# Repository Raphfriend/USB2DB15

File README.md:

# USB2DB15 - Supergun Adapter  

A simple ATmega328P-based USB-to-DB15 adapter designed for use with a Supergun or Neo Geo system.

<p align="center">
  
 <br>
  <b>USB2DB15 with a Sega Astro City Mini Arcade Stick</b><br>
<br>
	</p>  	

### 1. Features:

- USB input to support most modern HID compatible controllers
- 1ms polling, meaning a low latency and fast response from the USB2DB15
- Open-source firmware, so everyone in the community can collaborate
- DB15 pinout standard, ready for Neo Geo, Minigun, and HAS Superguns
- 4 customizable and storable mapping configurations
- 10 customizable and storable controller profiles
- Status LED
- Protection circuit for your beloved controllers

### 2. Technical information:

The USB2DB15 adapter is an open-source device based on an AVR microcontroller. It adapts a USB controller for use with a JAMMA PCB through a Supergun or with Neo Geo hardware that has controller ports. A variety of common controllers are supported, including controllers that follow the PS3/PS4 DualShock, PS5 DualSense, and Xbox 360/One protocols. Due to the diversity of controllers and differing standards, some controllers may not work with USB2DB15 or may not work as intended. Please be patient during these early stages. Feel free to contact the developers with additional information or requests for help with your USB2DB15 adapter through our communication channels (GitHub, Discord, and the Arcade-Projects forum).

We are using a modified USB Host Shield 2.0 library for controller IDs that aren't natively supported.

The 8BitDo M30 Mega Drive and NEOGEO controllers are supported through their original 2.4 GHz USB receivers and through a wired USB connection. The receiver versions use XInput mode; the wired versions use their USB controller mode.

With regard to hardware, there are currently three options:

- A Custom PCB that accommodates and integrates an Arduino Pro Mini, USB Shield Mini and other relevant hardware.
- USB2DB15 2.0 Ver, a pre-built single PCB that incorporates all required hardware in a standalone form.
- USB2DB15 CS Ver, similar to 2.0 Ver but focused on PCB consolization. In place of the DB15 controller connector, this board has screw terminals and a 20-pin header compatible with a 20-pin Brook Fighting Board Cable.

Alternatively, you can simply use a breadboard to connect it all together.

If you are building the open source version for yourself, a basic understanding of Arduino and its programming environment is required. Visit [arduino.cc](https://arduino.cc) to help you get started.

<p align="center">
  
 <br>
  <b>USB2DB15 pinout standard</b><br>
<br>

### 3. Open Source Required Hardware:

* The USB2DB15 uses an ATmega328P AVR. Any Arduino that uses this microcontroller, such as the Pro Mini, Nano, or Uno, is suitable. The custom PCB accommodates an Arduino Pro Mini and USB Host Shield Mini.
* USB Host Shield Mini if using an Arduino Pro Mini / Nano. Full sized USB Host Shield for Uno.
* An FTDI programmer is required for the Arduino Pro Mini. This is not required if using an Arduino Nano or Uno.
* A USB2DB15 custom PCB or a breadboard to complete all connections between the AVR and USB Host Shield.
* DB15 female connector.

<p align="center">
  
 <br>
  <b>Arduino Pro Mini and Usb Host Shield Mini</b><br>
<br>
	</p>  	

If using the custom PCB with an Arduino Pro Mini and USB Host Shield Mini, a BOM is available in the repository's `BOM` folder.

##### Jumper settings:

- SJ1: Bridge this jumper ONLY to disable 5V protection.
- SJ2: Bridge this jumper ONLY to enable 5V protection.
- JP2: 5V solder point (see information below regarding USB VBUS).

Due to variations among Pro Mini PCBs, A4 and A5 may be in different locations. Please pay attention to this.

<p align="center">

 <br>
  <b>Custom PCB 1.2 for Arduino Pro Mini</b><br>
</p>

### 4. Installation:

Download the <a href="https://github.com/Raphfriend/USB_Host_Shield_2.0">USB Host Shield 2.0 library</a> and install it in the Arduino IDE. Open the INO file (`RFUSB_to_DB15.ino`) and upload it to your AVR.

If you have a USB Host Shield Mini, you will need to cut the trace after the 2.2 kΩ resistor near the USB VBUS pin. Solder a wire from JP2 on the custom PCB to the through-hole via labeled `5V`, as shown in the picture below.

This enables devices that require +5 V power to function correctly, because the USB Host Shield Mini supplies only 3.3 V to the VBUS pin of the USB connector by default.

The remainder is plug and play.

If you are not using a prefabricated PCB, see the schematic for wiring information.

#### 4.1. Arduino Pro Mini + USB Shield Mini:
[See FLASHING.md for instructions.](FLASHING.md)

#### 4.2. Arduino Uno + USB Host Shield:

1. Install Arduino IDE.
2. Mount the USB Host Shield to the Arduino Uno correctly.
3. Connect the Arduino Uno to your PC via its USB Type-B cable.
4. In the Arduino IDE, navigate to "Tools" -> "Board" -> "Arduino AVR Boards" and select "Arduino Uno".
5. In the Arduino IDE, navigate to "Tools" -> "Port" and choose the Arduino device.
6. In the Arduino IDE, navigate to "Tools" -> "Programmer" and select "AVRISP MKII".
7. Find the library path in Arduino IDE: "File" -> "Preferences" -> "Sketchbook location", then copy the required `USB_Host_Shield_20` library into the `libraries` directory.
8. Open the firmware INO file (`RFUSB_to_DB15.ino`).
9. With the Arduino Uno connected to your PC, select "Sketch" -> "Upload".
10. Wait for the sketch to upload, as indicated in the console window at the bottom of the Arduino IDE.

### 5. Supported Controllers:

[See Compatibility.md for a detailed list of supported controllers.](COMPATIBILITY.md)

#### 5.1. DualShock 4 and DualSense left analog stick

USB DualShock 4 and DualSense controllers can use the left analog stick as an additional digital directional input. The analog stick and physical D-pad are combined, so either input can control the DB15 directions.

For these controllers, the firmware applies Hit Box-style SOCD cleaning after combining both directional sources:

| Simultaneous directions | DB15 output |
| --- | --- |
| Left + Right | Neutral |
| Up + Down | Up |

This prevents opposite horizontal directions from reaching the game and makes vertical conflicts deterministic. The feature is enabled automatically for supported DualShock 4 and DualSense USB reports; no separate profile or user configuration is required.

#### 5.2. Release mode and Serial diagnostics

`RFUSB_to_DB15/BuildConfig.h` contains the following build-time setting:

```cpp
#define USB2DB15_RELEASE_MODE 1
```

Use release mode (`1`) for competitive play. It disables all firmware Serial output, preventing diagnostic messages from occupying the serial transmit buffer and delaying controller polling or DB15 updates.

Use diagnostic mode (`0`) when troubleshooting a controller:

```cpp
#define USB2DB15_RELEASE_MODE 0
```

Upload the firmware again after changing the setting, then open the Arduino Serial Monitor at 115200 baud. Set the value back to `1` and upload again before competitive play.

### 6. Software Usage
#### 6.1 Controller Profiles
The adapter can store profiles for up to 10 unique controller models*. Controllers of the same make and model share profiles.
Each controller has 4 associated profiles. If you plug in an 11th controller, the system replaces the oldest controller you have set up, then the next oldest for the 12th, and so on. This may require you to set up older controllers again when you resume using them.

These can be accessed by pressing SELECT (COIN) plus one of the four directions.
For example, press SELECT + UP for the first profile, SELECT + RIGHT for the second, and so on.
The adapter will remember what profile you were using and automatically switch to it when you use the controller again.

To change a profile's key bindings, first switch to the profile you want to set up.
While holding SELECT for at least 3 seconds, press buttons 1–6 in order. Then release SELECT to lock in the binding.

*XBox One controllers appear to the system as the same make and model and thus use the same profiles even if they are different controllers.

### Shell

[AvramCE](https://twitter.com/avramce) has created a [3D printed case](https://www.thingiverse.com/thing:5170415) that you can print for your USB2DB15.

### How does it look in real life?

When you put all the parts together, USB2DB15 should look like this.
<p align="center">
  
	 <br>
  <b>Setup and photo by <a href="https://twitter.com/Focux11">@Focux</a> </b>
	</p>  	
<p align="center">
  
	 <br>
    <b>Setup and photo by <a href="https://twitter.com/_atrac17">@_atrac17</a> </b>
	</p>  	

### Support this project

If you have found USB2DB15 useful, please consider funding it and making a donation so that we may continue our work by obtaining additional controllers, equipment, and everything else required to keep this project alive and growing.

### Is this product available to buy? Yes!

We sell USB2DB15 directly. You will receive a premium edition that is slightly different from the open-source version but has the same features.
You can choose from a variety of shell color options, and you will get detailed instructions following your purchase.
There are two versions: the standard DB15 and the CS Ver., which is targeted toward JAMMA PCB consolization.

<a href="https://ko-fi.com/s/b6c3d01043">Access our shop by clicking here or on the images below. </a>

<p align="center">
<a href="https://ko-fi.com/s/b6c3d01043">
  
</p>

<p align="center">
<a href="https://ko-fi.com/s/b6c3d01043">
  
</p>

<p align="center">
<a href="https://ko-fi.com/s/b6c3d01043">
  
</p>

<p align="center">
<a href="https://ko-fi.com/s/b6c3d01043">
  
</p>

### Where can I get more help if I need it?

Via Arcade-Projects forum or RF Projects Discord server.

<p align="center">
<a href="https://www.arcade-projects.com/forums/index.php?thread/14205-open-source-usb-to-db15-for-supergun-adapter/">
  
</p>

<p align="center">
<a href="https://discord.gg/XKCjtpH">
  
</p>

### LEGAL

Neither USB2DB15 nor any of its maintainers is associated with or endorsed by Nintendo, Sony, SNK, Microsoft, 8BitDo, Sega, Brook, Mad Catz, Nacon, Honcam, DaemonBite, Buffalo, Qanba, Razer, Retro-Bit, Toodles, Hori, or any other company not explicitly indicated. All other brands and product names are the property of their respective holders.

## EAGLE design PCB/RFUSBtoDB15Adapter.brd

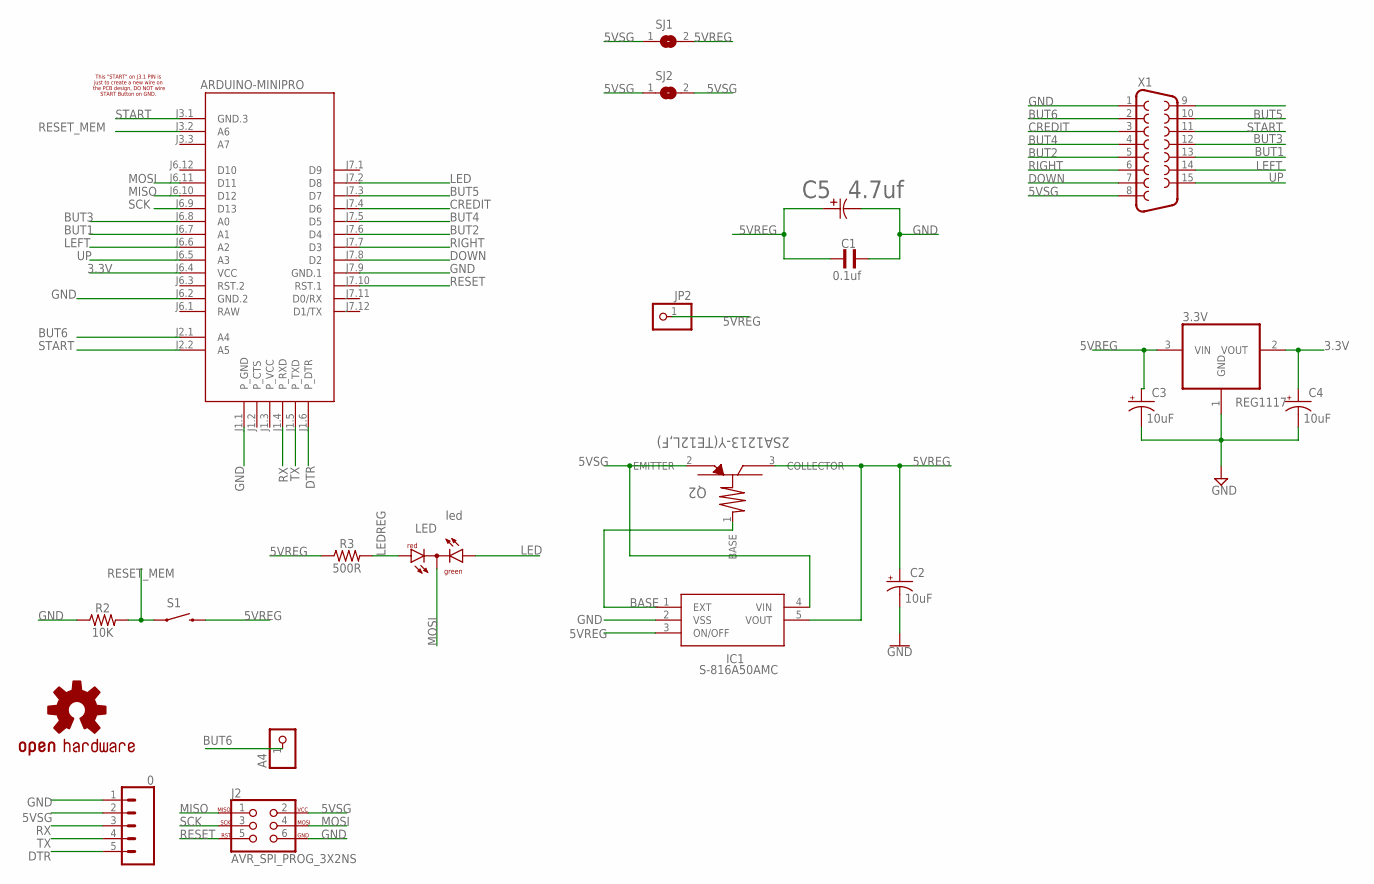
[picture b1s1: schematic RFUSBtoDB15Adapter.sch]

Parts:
3.3V: REG1117; SOT223
A4: 0; 1X01
ARDUINO-MINIPRO: ARDUINO-PRO-MINI-5.0V; ARDUINO-PRO-MINI
C1: 0.1uf; WCAP-CSGP_0805_REFLOW
C2, C3, C4: 10uF; EIA3216
C5: 4.7uf; CAPMP3.4X1.6_1.8N_KEM
IC1: S-816A40AMC-BAPT2U; SOT95P275X130-5N; MANUFACTURER_PART_NUMBER S-816A50AMC
J1: 0; 1X05
J2: AVR_SPI_PROG_3X2NS; 2X3-NS
JP2: JP2; 1X01
LED: led; DUOLED-C-5MM
LOGO1: OSHW-LOGOS; OSHW-LOGO-S
Q2: 2SA1213-Y(TE12L,F); PW-MINI_TOS
R2: 10K; 0805
R3: 500R; 0805
S1: RS032G05A3SM-SPST-MOMENTARY-SWSMD-1101NE; TACTILE-SWITCH-1101NE
SJ1, SJ2: SJ
X1: F15HP

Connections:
3.3V: 3.3V.2 (VOUT), ARDUINO-MINIPRO.J6.4 (VCC), C4.+
5VREG: 3.3V.3 (VIN), C1.2, C2.+, C3.+, C5.1, IC1.3 (ON/OFF), IC1.5 (VOUT), JP2.1, Q2.3 (COLLECTOR), R3.1, S1.2, SJ1.2
5VSG: IC1.4 (VIN), J1.2, J2.2, Q2.2 (EMITTER), SJ1.1, SJ2.1, SJ2.2, X1.8
BASE: IC1.1 (EXT), Q2.1 (BASE)
BUT1: ARDUINO-MINIPRO.J6.7 (A1), X1.13
BUT2: ARDUINO-MINIPRO.J7.6 (D4), X1.5
BUT3: ARDUINO-MINIPRO.J6.8 (A0), X1.12
BUT4: ARDUINO-MINIPRO.J7.5 (D5), X1.4
BUT5: ARDUINO-MINIPRO.J7.3 (D7), X1.10
BUT6: A4.1, ARDUINO-MINIPRO.J2.1 (A4), X1.2
CREDIT: ARDUINO-MINIPRO.J7.4 (D6), X1.3
DOWN: ARDUINO-MINIPRO.J7.8 (D2), X1.7
DTR: ARDUINO-MINIPRO.J1.6 (P_DTR), J1.5
GND: 3.3V.1 (GND), ARDUINO-MINIPRO.J1.1 (P_GND), ARDUINO-MINIPRO.J6.2 (GND.2), ARDUINO-MINIPRO.J7.9 (GND.1), C1.1, C2.-, C3.-, C4.-, C5.2, IC1.2 (VSS), J1.1, J2.6, R2.1, X1.1
LED: ARDUINO-MINIPRO.J7.2 (D8), LED.AX (AG)
LEDREG: LED.AR, R3.2
LEFT: ARDUINO-MINIPRO.J6.6 (A2), X1.14
MISO: ARDUINO-MINIPRO.J6.10 (D12), J2.1
MOSI: ARDUINO-MINIPRO.J6.11 (D11), J2.4, LED.C
RAW: ARDUINO-MINIPRO.J6.1 (RAW)
RESET: ARDUINO-MINIPRO.J7.10 (RST.1), J2.5
RESET_MEM: ARDUINO-MINIPRO.J3.2 (A6), R2.2, S1.1
RIGHT: ARDUINO-MINIPRO.J7.7 (D3), X1.6
RX: ARDUINO-MINIPRO.J1.4 (P_RXD), J1.3
SCK: ARDUINO-MINIPRO.J6.9 (D13), J2.3
START: ARDUINO-MINIPRO.J2.2 (A5), ARDUINO-MINIPRO.J3.1 (GND.3), X1.11
TX: ARDUINO-MINIPRO.J1.5 (P_TXD), J1.4
UP: ARDUINO-MINIPRO.J6.5 (A3), X1.15

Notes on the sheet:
This "START" on J3.1 PIN is just to create a new wire on the PCB design, DO NOT wire START Button on GND.

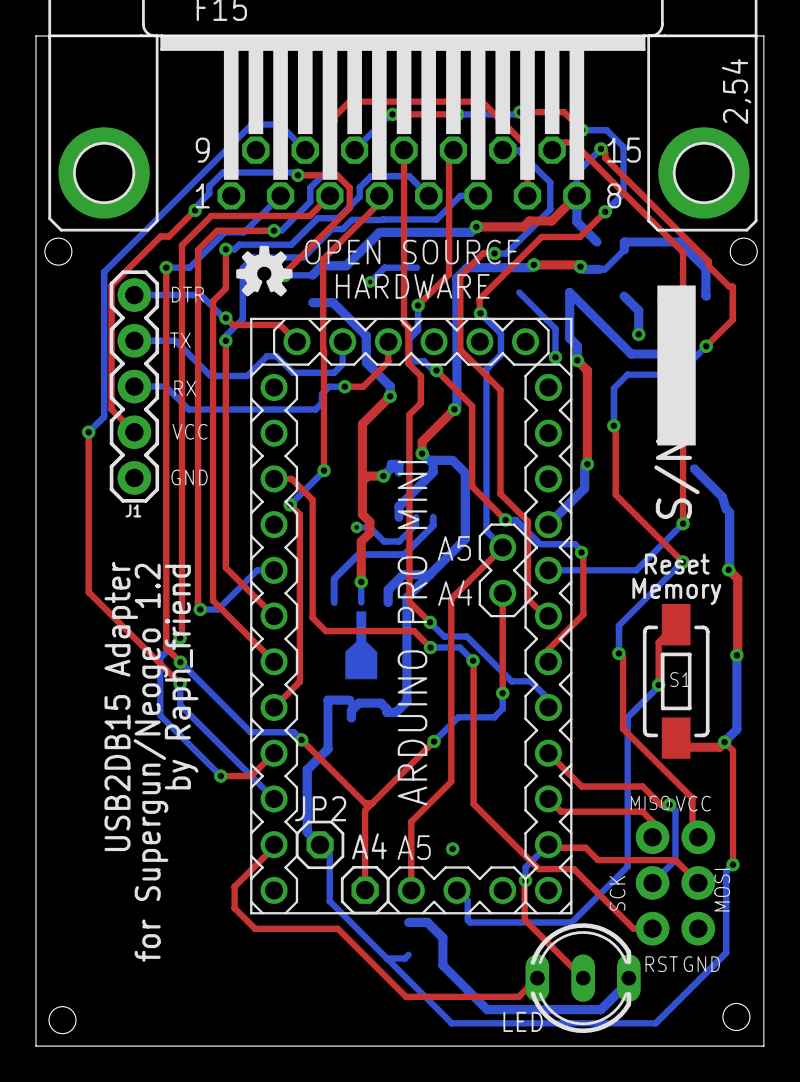
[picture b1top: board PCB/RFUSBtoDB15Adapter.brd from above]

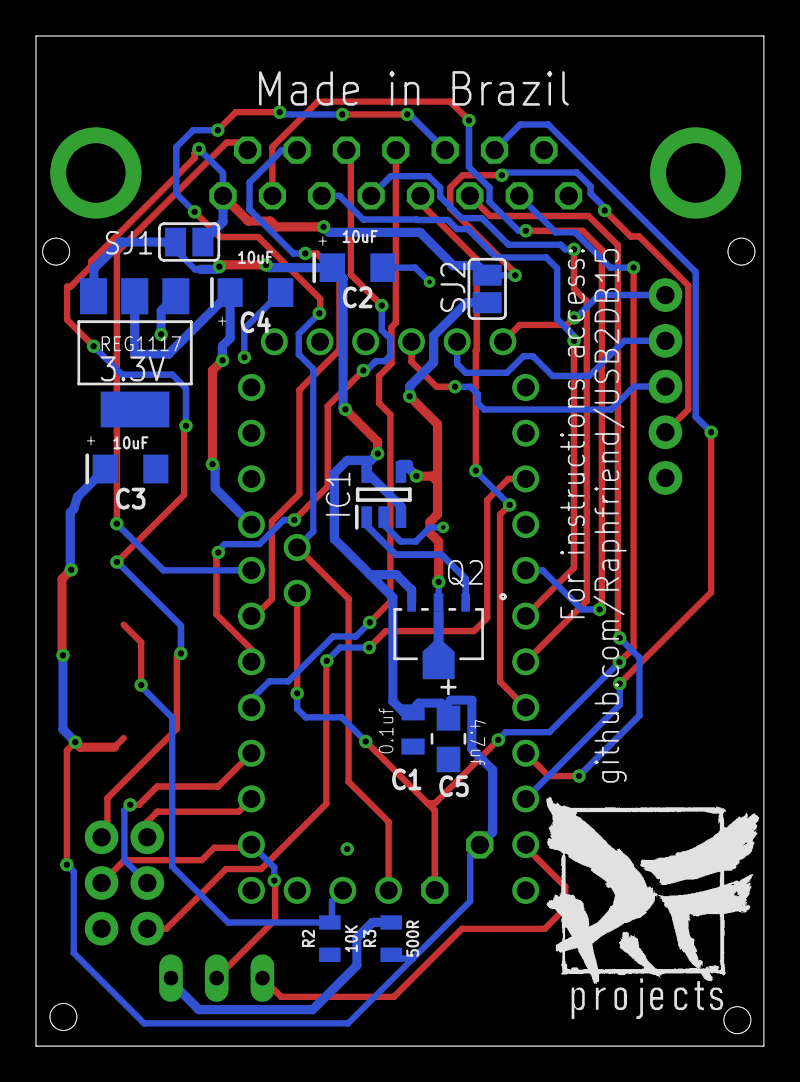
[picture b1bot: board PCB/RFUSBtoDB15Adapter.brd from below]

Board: 2 copper layers, 40.4 x 56.1 mm, 22 parts (13 on the bottom side), 27 nets.

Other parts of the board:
U$2: RF_LOGO

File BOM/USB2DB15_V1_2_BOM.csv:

Designator,Component,Footprint,LCSC Part #
3.3V,REG1117,SOT223,
IC1,S-816A40AMC-BAPT2U,SOT95P275X130-5N,
Q2,2SA1213-Y(TE12L F),PW-MINI_TOS,
C1,0.1uf,0805 SMD Ceramic,
"C2, C3 and C4 are optional",10uF,EIA3216,
C5,4.7uf,CAPMP3.4X1.6_1.8N_KEM,
R2,10K,0805 SMD,
R3,33R-500R,0805 SMD,
S1,TACTILE-SWITCH,3x6x2.5mm SMD,
ARDUINO,Arduino Pro Mini 5 or 3V,,

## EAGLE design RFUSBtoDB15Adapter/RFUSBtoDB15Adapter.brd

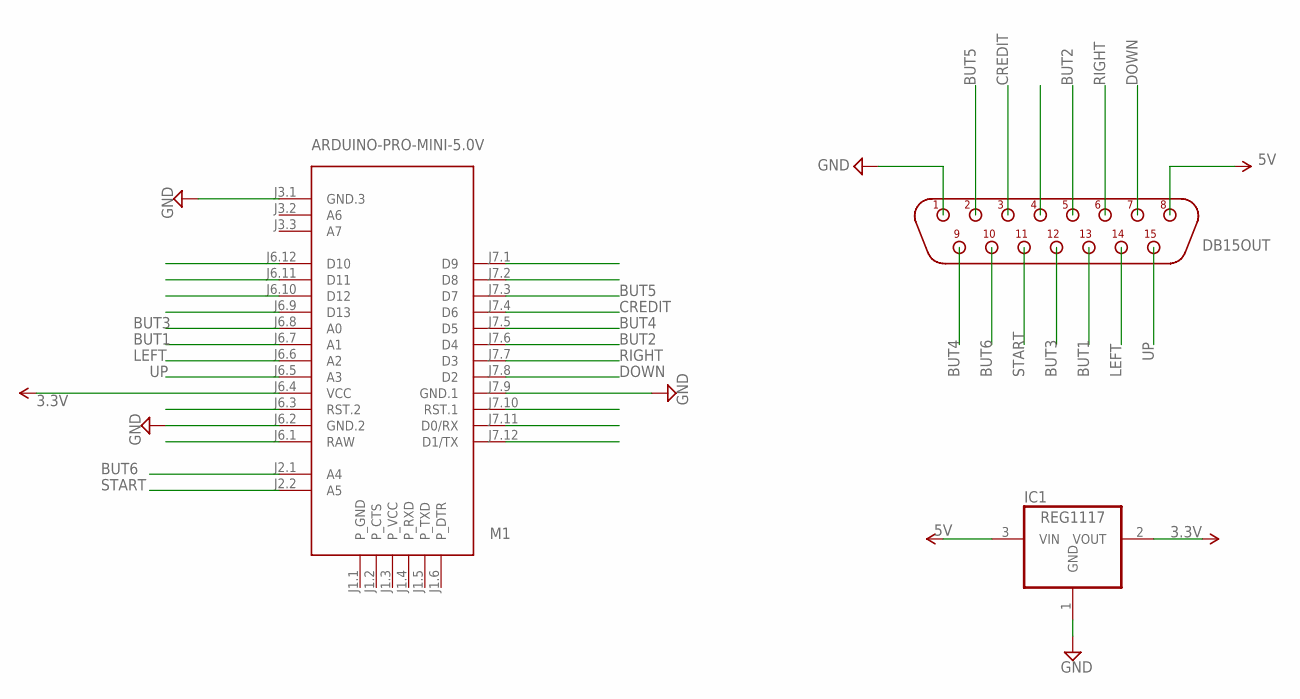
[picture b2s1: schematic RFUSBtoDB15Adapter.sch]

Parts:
DB15OUT: DB15M/90; D-15M/90
IC1: REG1117; SOT223
M1: ARDUINO-PRO-MINI-5.0V; ARDUINO-PRO-MINI

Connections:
3.3V: IC1.2 (VOUT), M1.J6.4 (VCC)
5V: DB15OUT.8, IC1.3 (VIN)
BUT1: DB15OUT.13, M1.J6.7 (A1)
BUT2: DB15OUT.5, M1.J7.6 (D4)
BUT3: DB15OUT.12, M1.J6.8 (A0)
BUT4: DB15OUT.9, M1.J7.5 (D5)
BUT5: DB15OUT.2, M1.J7.3 (D7)
BUT6: DB15OUT.10, M1.J2.1 (A4)
CREDIT: DB15OUT.3, M1.J7.4 (D6)
DOWN: DB15OUT.7, M1.J7.8 (D2)
GND: DB15OUT.1, IC1.1 (GND), M1.J3.1 (GND.3), M1.J6.2 (GND.2), M1.J7.9 (GND.1)
LEFT: DB15OUT.14, M1.J6.6 (A2)
RIGHT: DB15OUT.6, M1.J7.7 (D3)
START: DB15OUT.11, M1.J2.2 (A5)
UP: DB15OUT.15, M1.J6.5 (A3)

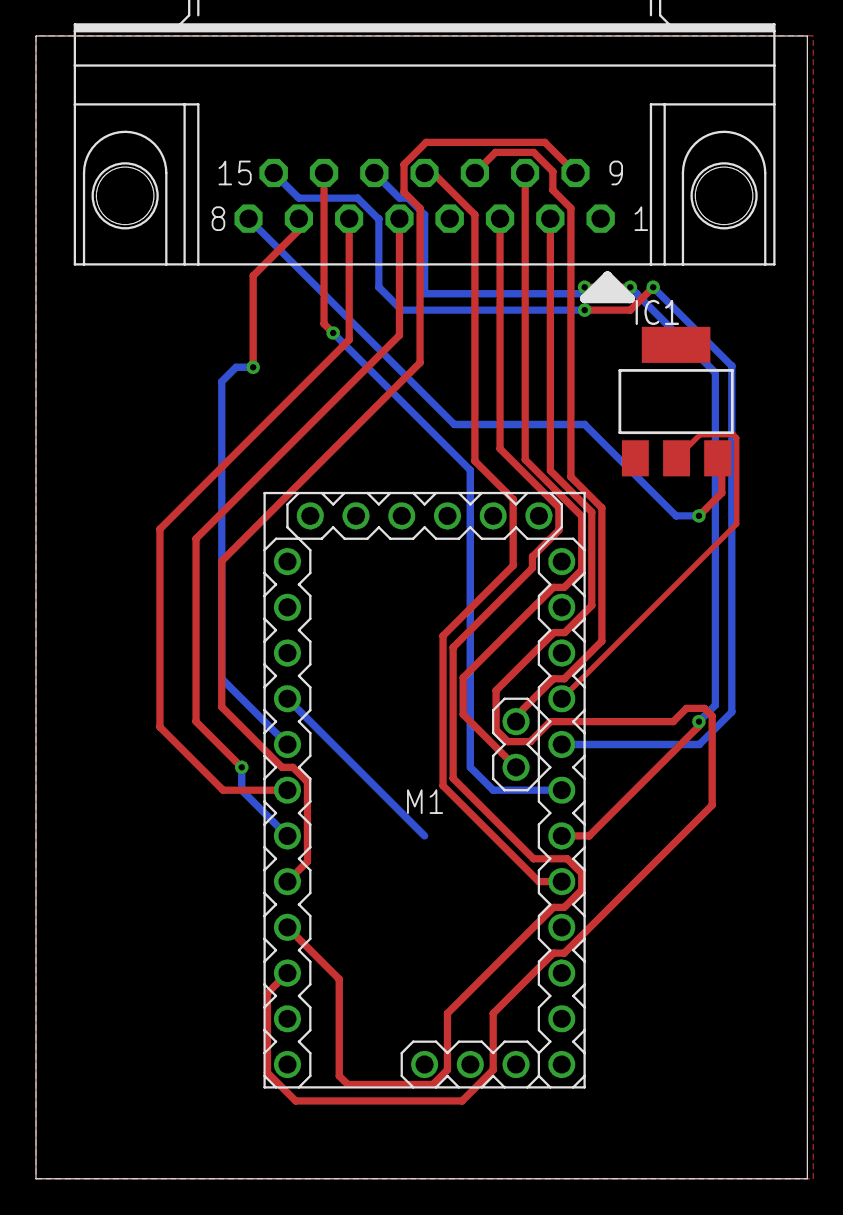
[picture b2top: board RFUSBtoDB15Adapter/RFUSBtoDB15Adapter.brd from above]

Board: 2 copper layers, 42.9 x 63.5 mm, 3 parts (0 on the bottom side), 15 nets.

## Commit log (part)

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2020-06-09 Add files via upload
    DS4 full working.
2020-06-29 Create pcb
2020-07-21 Add files via upload
    DS3 implemented
2020-08-03 Add files via upload
    Fixed X and O button for PS3
2020-08-04 Add files via upload
    Some cleaning on code
2020-08-09 Add files via upload
    Retrobit Sega Saturn wireless 8bit attempt to support
2020-08-10 Structural change and PCB
    Directory change and new board design.
2020-08-10 Create RFUSBtoDB15Adapter.png
    PCB Layout
2020-08-11 Exit ParseHIDData when controller unknown
2020-08-11 Exit ParseHIDData Early if no controller found
2020-08-11 Create USB2DB15-Adapter-schematic.pdf.pdf
    Schematic in PDF
2020-08-11 New PCB
    PCB updated
2020-08-11 Update RFUSBtoDB15Adapter.brd
    Changes on PCB
2020-08-11 Update RFUSBtoDB15Adapter.png
    New design
2020-08-12 Add support for USB connected LED
2020-08-13 Updates
    Schematic, PCB and code updates.
2020-08-13 Update RFUSB_to_DB15.ino
    Updated
2020-08-13 Update RFUSB_to_DB15.ino
    Brook Universal PCB support on PS4 mode
2020-08-13 Create LICENSE
2020-08-13 Schematic PDF
    Fix on extension
2020-08-13 PCB
    Some changes
2020-08-14 Add support for 8bitdo controllers
2020-08-15 Adds a polling override value
2020-08-17 PCB
    PCB design updated
2020-08-17 Update README.md
    Removed some unnecessary jumpers and PCB revised.
2020-08-21 Added support to HORI Real Arcad Pro - Soul Calibur VI Edition for Xbox One
2020-08-22 Add Support for Xbox and PS3 Profiles
2020-08-22 First attempt to save profiles.
2020-08-22 Clean Up
    Removed unused code
    Changed Constants from variables to defines
2020-08-23 Fix Device Button defines
    Fixes a skipped number in the button enum in device description. Prevented looping
2020-08-23 Add Hid Controller and Drivers
2020-08-23 Add Hid support to USB2DB15
    Started clean up of main project file
2020-08-23 Change UPCB VID and PID
2020-08-23 Added Function Comments to Drivers.cpp
2020-08-23 Added Function Docs to HIDController
2020-08-23 Clean up
    Removed Dead code from RFUSB_to_DB15
    Fixed some bugs
2020-08-23 Update Documentation
2020-08-23 Added Xbox to compatibility List
2020-08-23 Turn off xbox rumble
2020-08-23 Fix Xbox Rumble
2020-08-24 Fixed DPad Down Left for HID
2020-08-24 Add Mad Cats Streetfighter 4
2020-08-25 Add Function Doc Strings for XBoxOne
2020-08-25 Add Documentation to Profile
2020-08-25 Add Documentation to Controller.h
2020-08-25 Add comments to USB2DB15
2020-08-25 Add Documentation to PS3Controller
2020-08-25 Clean up some missing line breaks
2020-08-25 Invert C and Z buttons for 8BitDo
2020-08-27 PCB update
    Small changes
2020-08-30 Create EEPROM manager
2020-08-30 Move Defualt Profiles to EEPROM
2020-08-30 Remove Unneeded Library from Eeprom Manager
2020-08-30 Add Click Support to Controller
2020-08-30 Add Click Support To XBox Controllers
2020-08-30 Add Click Support to PS3 Controllers
2020-08-30 Add button clicked to HID Controller
2020-08-30 Fix Click Support For HIDController
    Add some fancy MASK manipulation to reduce some giant switch statements. Probably slower but easier to read
2020-08-30 Refactor USB2DB15 for bindable profiles
2020-08-30 Add Function Docs
2020-09-02 Add VID and PID accessors to controllers
2020-09-02 Add Profile Block support to EEPROM Manager
2020-09-02 Add Support for Per Device Profiles to USB2DB15
2020-09-02 Update Profile Information in README
2020-09-02 Add XBoxOne exception
2020-09-11 Add files via upload
    LED Class to control the MODE LED connected to digital PIN 8.
2020-09-11 Update USB2DB15.cpp
    Additional code to support LED class
2020-09-12 Added LED & Reset
2020-09-12 Change LED from a class to namespace
    Encapsulate all functions and code for LED control into a cpp file
2020-09-12 Updated Reset EEPROM Logic
    Removed unnesscary temp variable buttonValue
    Removed resetEEPROM and instead let the EepromManager handle the reset.
2020-09-12 Moved FactoryReset into USB2DB15
    Reset pid and vid values to inital state
2020-09-12 Increase Button Threshold to 500
2020-09-12 WOL improvements to reset
    Added a Guard Lock to the reset function so it can only happen once per button press
    Increased Reset Threshold to 800
    Made LED blink 5 times
    Prints out "Resetting" while reseting
    Sets inital profile block to 0
2020-09-12 Adds a paramter to the LED::Blink() function to stipulate number of blinks and speed of blinks
    Removes:
    #define BLINK_HALF_LENGTH
    Adds a second parameter to:
    LED::Blink();
    To stipulate the speed of blinking.
2020-09-12 PCB Update
    LED status and MEMORY RESET now supported
2020-09-12 Changed Magic numbers in LED to constants
2020-09-12 Update LED.cpp Comment
2020-09-12 Small Typo Fix
2020-09-14 Added support for Nacon Daija (ps3, ps4)
2020-09-15 Support for Honcam stick
2020-09-16 Update
    Donation and schematic PDF
2020-09-16 Update
    Link fix
2020-09-16 Added Generic SNES pad
    Added Generic SNES pad
    Refactored Retrobit Saturn Wireless
2020-09-16 8BitDo
    - Added support for SFC30
    - Modified M30 implementation to support it via D-INPUT mode rather than MacOS mode.
    - Improved M30 mapping.
2020-09-18 8BitDo BT Rec
    Added support for 8BitDo Bluetooth NES & SNES Receivers.
    Updated CHANGELOG & COMPATIBILITY to reflect this.
2020-09-19 Update CHANGELOG.md
    Added info about USB Host Shield 2.0 library files.
2020-09-19 Update COMPATIBILITY.md
    Added Hori Fighting Stick Mini 4
    Added info to controllers requiring USB HOST SHIELD 2.0 library update
2020-09-19 Update COMPATIBILITY.md
    Typo fix
2020-09-19 Hori Fighting Stick V3
    Adds support fir Hori Fighting Stick V3
2020-09-20 Update COMPATIBILITY.md
    Added extra information
2020-09-20 Update CHANGELOG.md
    Added info about M30 and 8BitDo wireless receivers
2020-09-20 Update CHANGELOG.md
    Added information about updated USB Shield updated files
2020-09-20 Fixes START & SELECT being reversed
    Small fix for the Honcam joystick to rectify START & SELECT buttons being reversed.
2020-09-21 Update COMPATIBILITY.md
    Added a few extra recently confirmed controllers
2020-09-29 Added Support for Qanba Obsidian
2020-10-02 Minor Tidy Up of comments & code formatting
2020-10-04 Extends support for the Mad Catz SFIV PS3 stick to support both versions of the controller.
2020-10-04 Xbox 360 support
    Experimental implemtation. Needs testing and verification.
2020-10-05 Update XBoxUSBController.cpp
    Added basic analog support for the purpose of reading 8BitDo DPADs.
2020-10-05 Analog Support
    Basic analog support for XBox 360 & PS3.
2020-10-05 Update PS3Controller.cpp
    Added missing or symbol to line 81
2020-10-05 Update PS3Controller.cpp
    Removed unnecessary LED stuff from PS3Controller::Connected() (sorry was something I was experimenting with and forgot to remove)
2020-10-09 Xbox Mapping and Analog
    Xbox 360 and Xbox One mapping issue fixed.
    Xbox One analog support added.
    PS3 analog support refined and bug fixed.
    Added serial output control.
2020-10-09 PCB Update
2020-10-09 Small fix
2020-10-12 Qanba Crystal
    Qanba Crystal implementation (PS3 & PS4 modes)
2020-10-14 Add a Null button for unbound keys
2020-10-14 Clear Unbound Profile buttons on early exit
2020-10-15 Update RFUSB_to_DB15.ino
    Synced version number in main INO file.
2020-11-11 Update README.md
    Just a small fix.
2020-11-14 Revert "Merge pull request #49 from Raphfriend/Frank-fjs-patch-2"
    This reverts commit 7b12d3794918d97649cff50f625bace1fb1e8581, reversing
    changes made to aff03f1f39435062884922ed897bb8d5cb139e61.
2020-11-14 Revert "Revert "Merge pull request #49 from Raphfriend/Frank-fjs-patch-2""
    This reverts commit 92c274d6be7aaaae423d808fde2ac72dc8ca5392.
2020-11-14 Revert "Merge pull request #50 from Raphfriend/Raphfriend-patch-3"
    This reverts commit 733a5ab4eaf5c36f465fbf0934cd90ffc9b5e959, reversing
    changes made to 7b12d3794918d97649cff50f625bace1fb1e8581.
2020-11-14 Revert "Update README.md"
2020-11-18 Daemonbite-Support
    Initial support for Daemonbite-Support
2020-11-19 Update drivers.cpp
    Comments fixed.
2020-11-20 Update drivers.h
    Added notes for Arduino Leonardo VID and PID
2020-11-20 Update COMPATIBILITY.md
    Small fix
2020-12-09 Update COMPATIBILITY.md
    - NES & SNES Bluetooth receviers tested compatible with the following controllers:
    - 8BitDo Arcade Stick (November 2020 version) on Switch mode and Firmware 1.03
2020-12-19 Add support for Astro City Mini Arcade Stick
2020-12-19 Update CHANGELOG.md
    Changes for Astro City Mini Arcade Stick
2020-12-19 Update COMPATIBILITY.md
    Support now Astro City Mini Arcade Stick
2021-01-19 Add support for Neo Geo Mini Pad
2021-01-19 Update drivers.h
    Fixed the driver alphabet order.
2021-01-19 Update drivers.h
    - Fixed alphabet order for IDs
    - Added Razer Panthera EVO ID
2021-01-21 Update CHANGELOG.md
    Support for Neo Geo Mini Pad and Razer Panthera EVO
2021-01-21 Update COMPATIBILITY.md
    Support for RAZER Panthera EVO and Neo Geo Mini Pad
2021-02-25 DualSense support
    Added support for Playstation 5 DualSense
2021-02-27 Update drivers.cpp
    Clean up code a bit and fix a comment
2021-02-27 Update drivers.cpp
    Remove unneeded code
2021-03-10 Brook FB
    Add support for Brook FIGHTING BOARD
2021-03-14 Brook FIGHTING BOARD PS3/PS4
2021-03-14 Update LICENSE
2021-03-25 Add Readme for Flashing/Updating USB2DB15 Software
2021-03-25 PR Feedback
2021-03-25 Woops
2021-03-31 Update CHANGELOG.md
    - Added Support for the XBOX 360 Hori Fighting Edge
    - Added Support for the PXN 0082 Arcade Stick
2021-06-20 Add section 4.2 for Arduino Mini Pro
2021-06-20 Update README.md
    Reorganize Sections 4.1 and 4.2
2021-06-20 Update README.md
    Section numbers
2021-09-09 Support for new controllers
2021-09-09 Update drivers.cpp
    Clean up Code Formatting
    Updated MADCATZ to not use 0xXF for buttons as that would conflict with the DPAD
2021-09-10 Adds support for Mat Catz Fight Stick Alpha
2021-09-10 Update COMPATIBILITY.md
    Small typo
2021-10-28 Zero delay PCB supported
2021-12-11 Add Hori Pokken Controller
2022-01-13 Squashed commit of the following:
    commit 5179368e148c8895b6ee6948061e4e767b4fc169
    Author: Dylan Enloe <enloed@gmail.com>
    Date: Wed Jan 12 20:37:27 2022 -0800
    Clean up Function names and comments
2022-01-13 Release Notes for Zero Delay Controller
2022-01-13 Update README.md
    Remove height modifiers from images to hopefully have them scale better
2022-01-13 New PCB and Schematics
    PCB/Schematics REV 1.2
2022-01-13 Update CHANGELOG.md
    New PCB and Schematics for Version 1.2 added with some fixes.
2022-05-13 Updates
    Added
    - FUSION Wired FightPad Gaming Controller for PlayStation 4
    Update Readme
2022-05-14 Fixes
2022-05-14 Pico Fighting Board GP2040
    - Support for new pads
    - Documentation updated
2022-05-15 Forgot link
2022-05-18 Logitech F310
2022-05-26 Update drivers.cpp
    Added Logitech F310
2022-05-26 Support for F310
2022-05-28 Added support for Qanba Drone (PID 2000, VID 2C222)
2022-06-01 Update drivers.h
    Add Control Pad for Astro City Mini - ACS-1002 and differentiate the device of SEGATOYS.
2022-08-03 Update drivers.h
    Add NEOGEOX Arcade Stick
2022-08-03 Update drivers.cpp
    Add NEOGEOX Arcade Stick
2022-12-23 New controllers and some fixes
2022-12-23 Fix Indentation on 8bitdo Case Statement
2023-06-18 Gerber PCB V1.2 uploaded
    - V1.2 Gerber
    - BOM V1.2
2023-12-05 Add Taito Egret II Mini Controller
    Add Taito VID
    Add Taito Egret II PID
    Add Driver for Taito Egret II
    Add Missing Deamon Comments
2023-12-05 Update change log
    Update Change Log and Compatibility with Egret II
2023-12-05 Fix Typo
2023-12-05 Fix Whitespace

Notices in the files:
parts and their libraries:
Arduino: Released under the Creative Commons Attribution 4.0 International License: http://creativecommons.org/licenses/by/4.0
SparkFun-Connectors: Licensing: Creative Commons ShareAlike 4.0 International - https://creativecommons.org/licenses/by-sa/4.0
